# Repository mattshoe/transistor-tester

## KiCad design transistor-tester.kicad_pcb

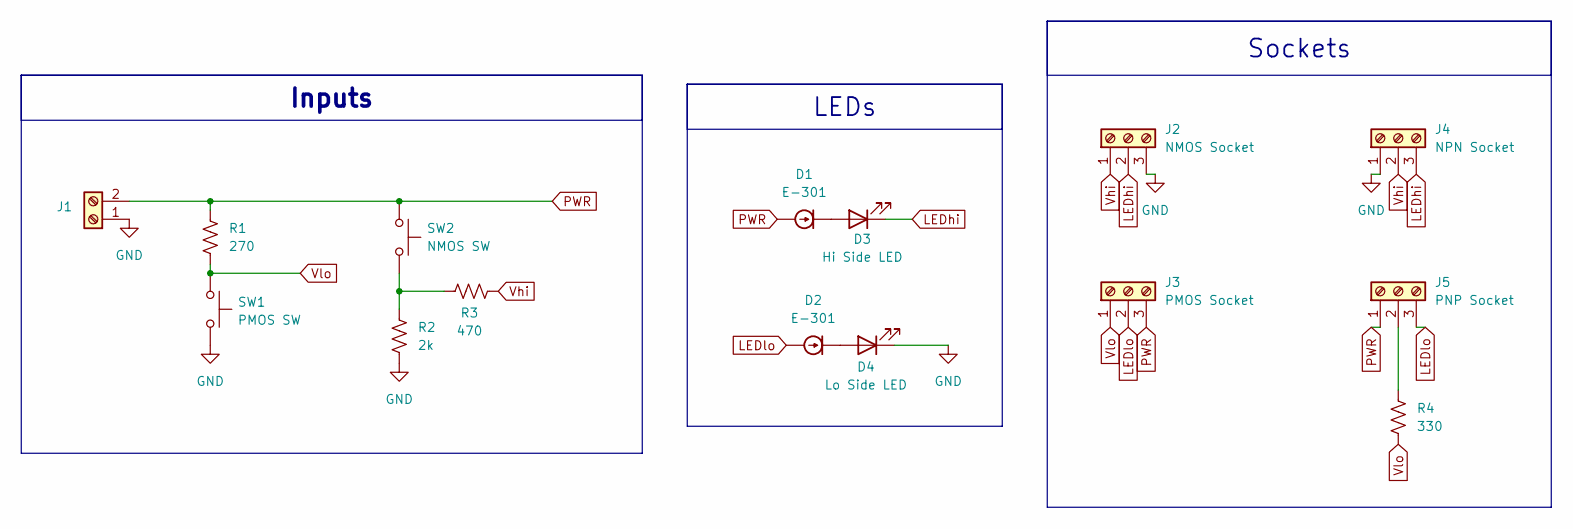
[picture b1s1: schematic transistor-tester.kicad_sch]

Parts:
D1, D2: E-301; D_A-405_P10.16mm_Horizontal
D3: Hi Side LED; LED_D3.0mm
D4: Lo Side LED; LED_D3.0mm
J1: Screw_Terminal_01x02; TerminalBlock_MaiXu_MX126-5.0-02P_1x02_P5.00mm
J2: NMOS Socket; TO-220-3_Vertical
J3: PMOS Socket; TO-220-3_Vertical
J4: NPN Socket; TO-220-3_Vertical
J5: PNP Socket; TO-220-3_Vertical
R1: 270; R_Axial_DIN0207_L6.3mm_D2.5mm_P10.16mm_Horizontal
R2: 2k; R_Axial_DIN0207_L6.3mm_D2.5mm_P10.16mm_Horizontal
R3: 470; R_Axial_DIN0207_L6.3mm_D2.5mm_P10.16mm_Horizontal
R4: 330; R_Axial_DIN0207_L6.3mm_D2.5mm_P10.16mm_Horizontal
SW1: PMOS SW; Switch_PushButton_m12x0.75
SW2: NMOS SW; Switch_PushButton_m12x0.75

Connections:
GND: D4.1 (K), J1.1, J2.3, J4.1, R2.1, SW1.2
LEDhi: D3.1 (K), J2.2, J4.3
LEDlo: D2.2 (A), J3.2, J5.3
unnamed: D1.1 (K), D3.2 (A)
unnamed: D2.1 (K), D4.2 (A)
unnamed: J5.2, R4.1
unnamed: R2.2, R3.1, SW2.2
PWR: D1.2 (A), J1.2, J3.3, J5.1, R1.2, SW2.1
Vhi: J2.1, J4.2, R3.2
Vlo: J3.1, R1.1, R4.2, SW1.1

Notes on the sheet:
Sockets
LEDs
Inputs

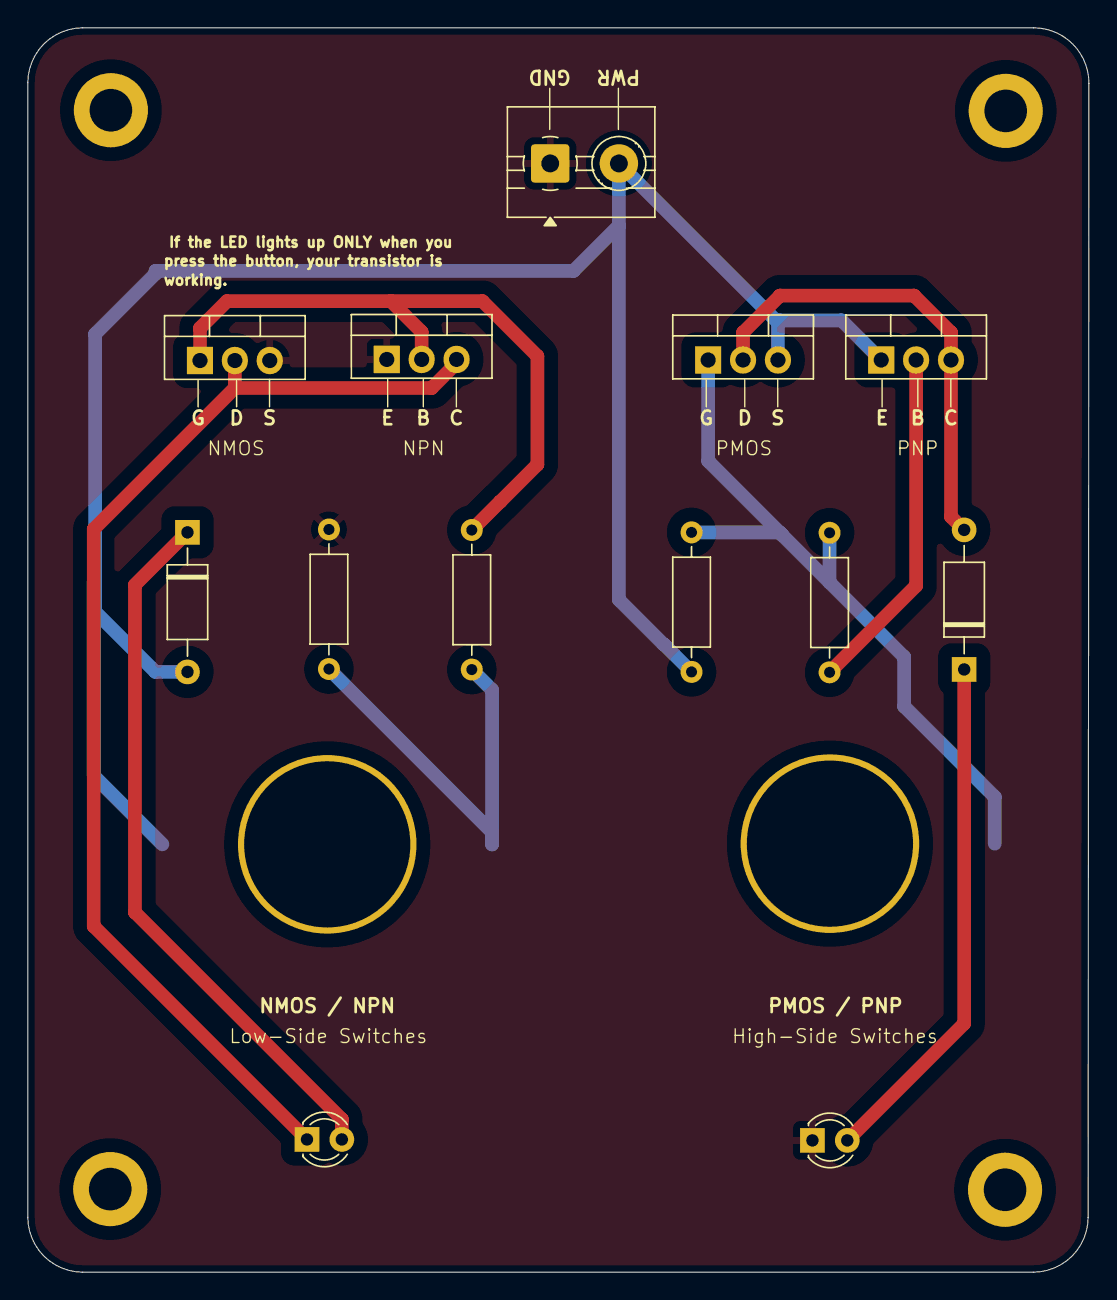
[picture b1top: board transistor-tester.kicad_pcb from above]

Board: 2 copper layers, 77.3 x 90.6 mm, 15 parts (0 on the bottom side), 10 nets.

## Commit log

2025-04-07 Initial design for transistor tester
2025-04-07 V1 submitted to JLCPCB
2025-04-19 latest
2025-04-19 Added product links to all kicad datasheet entries
